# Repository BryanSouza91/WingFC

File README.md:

# WingFC

> [!WARNING]
> ### ⚠️ REPOSITORY ARCHIVED & SUPERSEDED
> This original TinyGo implementation of WingFC has been archived and is preserved for historical reference.
>
> Active development has transitioned into two dedicated, first-class repositories within the **Ferrox-RC** ecosystem:
> - 🦀 **Firmware:** [**ferrox-rc/wingfc-rs**](https://github.com/ferrox-rc/wingfc-rs) — High-performance, zero-latency bare-metal Rust flight controller firmware for sub-250g wings and UAVs.
> - ⚡ **Hardware:** [**ferrox-rc/wingfc-hardware**](https://github.com/ferrox-rc/wingfc-hardware) — KiCad schematics, 4-layer PCB layouts, 3D mechanical models, and carrier board designs.

### Historical Version 0.3.0 (TinyGo Prototype)

WingFC is a specialized open-source embedded flight controller designed specifically for the rapidly growing sub-250g flying wing FPV (First-Person-View) market. The project's core mission is to provide a reliable, user-friendly, and highly customizable solution for hobbyists and enthusiasts building ultra-lightweight Unmanned Aerial Vehicles (UAVs).

The emphasis on the sub-250g weight class is a direct response to a patchwork of international regulations. Many aviation authorities worldwide, including the Federal Aviation Administration (FAA) in the U.S. and the European Union Aviation Safety Agency (EASA), have established a 250-gram weight threshold as a key regulatory distinction. UAVs below this weight are often considered a lower risk and are exempt from stricter rules, such as mandatory registration, Remote ID requirements, or more complex pilot licensing. By focusing on this market segment, WingFC enables hobbyists to build and fly FPV aircraft that can be legally operated in more places and with fewer bureaucratic hurdles, significantly lowering the barrier to entry for beginners and experienced pilots alike.

Powered by TinyGo, a Go compiler for microcontrollers, WingFC offers a robust and stable software platform. The project provides essential flight control features for elevon-equipped fixed-wing aircraft, including:

- **Stabilization Modes**: Offers flight stabilization to assist pilots, particularly for smooth, cinematic FPV footage and relaxed cruising.

- **Mixing**: Handles the complex mixing of aileron and elevator inputs for a fixed-wing flying wing platform, simplifying the aircraft's setup.

- **Safety Features**: Incorporates failsafe mechanisms to protect the aircraft and others in the event of signal loss.

- **Receiver Protocol Support**: Ensures broad compatibility with popular FPV communication standards, including FlySky's iBus, TBS's CRSF, and the open-source ELRS protocol, which is highly valued for its long-range capabilities and low latency in the FPV community.

The flight controller is engineered for a seamless integration into FPV flying wing airframes like the ZOHD Dart 250G or Alight Wing Aeronautics Flik, a prominent model in this market. The hardware's choice of the Seeed Studio Xiao nRF52840 Sense with an onboard IMU aligns with the project's goal of creating a compact, lightweight, and high-performance control system for these specific FPV drones.

## Getting Started

These instructions will get you a copy of the project up and running on your local machine for development and testing purposes. See deployment for notes on how to deploy the project on a live system.

### Prerequisites

What things you need to install the software and how to install them

```
- Go (TinyGo)
- Supported microcontroller (see docs)
```

### Installing

[Download source code](https://github.com/BryanSouza91/WingFC/releases/tag/v0.3.0)
Extract source code then navigate to the top directory of the source.
```
cd firmware/src
```

Plug in WingFC board via USB-C 

When the filesystem shows up on your computer, flash firmware to your board

```
tinygo flash -target=xiao-ble -tags=<ibus,crsf> firmware/src
```

## Deployment

Add additional notes about how to deploy this on a live system

- Flash the firmware to your supported board
- Connect servos and sensors as described
- Power up and calibrate according to instructions

## Built With

### Software
• [TinyGo](https://tinygo.org/) - Go compiler for microcontrollers  
• [Go](https://golang.org/) - Language
### Hardware
• [Seeed Studio Xiao nrf52840 Sense](https://wiki.seeedstudio.com/XIAO_BLE/) - Xiao nrf52840 Sense microcontroller with onboard IMU

## Supported Receiver Protocols

WingFC supports multiple RC receiver protocols for maximum compatibility:

- **iBus** (FlySky): Supports up to 18 channels (FS-A8S, FS-iA6B)
- **CRSF** (TBS): Supports up to 16 channels
- **ELRS** (open-source): Supports up to 16 channels (uses CRSF build)

## Contributing

Please read [CONTRIBUTING.md](https://github.com/BryanSouza91/WingFC/CONTRIBUTING.md) for details on our code of conduct, and the process for submitting pull requests to us.

## Versioning

We use [SemVer](http://semver.org/) for versioning. For the versions available, see the [tags on this repository](https://github.com/BryanSouza91/WingFC/tags).

## Authors

• Bryan Souza - Initial work - [BryanSouza91](https://github.com/BryanSouza91)
• truglodite - CRSF/ELRS finalization, feature additions - [truglodite](https://github.com/truglodite)

See also the list of [contributors](https://github.com/BryanSouza91/WingFC/contributors) who participated in this project.

## License

This project is licensed under the MIT License - see the [LICENSE](https://github.com/BryanSouza91/WingFC/blob/main/LICENSE) file for details

## Acknowledgments

• Hat tip to anyone whose code was used  
• Inspiration from open-source flight controllers  
• TinyGo and Go communities

## Footer

[GitHub Homepage](https://github.com/)
# WingFC

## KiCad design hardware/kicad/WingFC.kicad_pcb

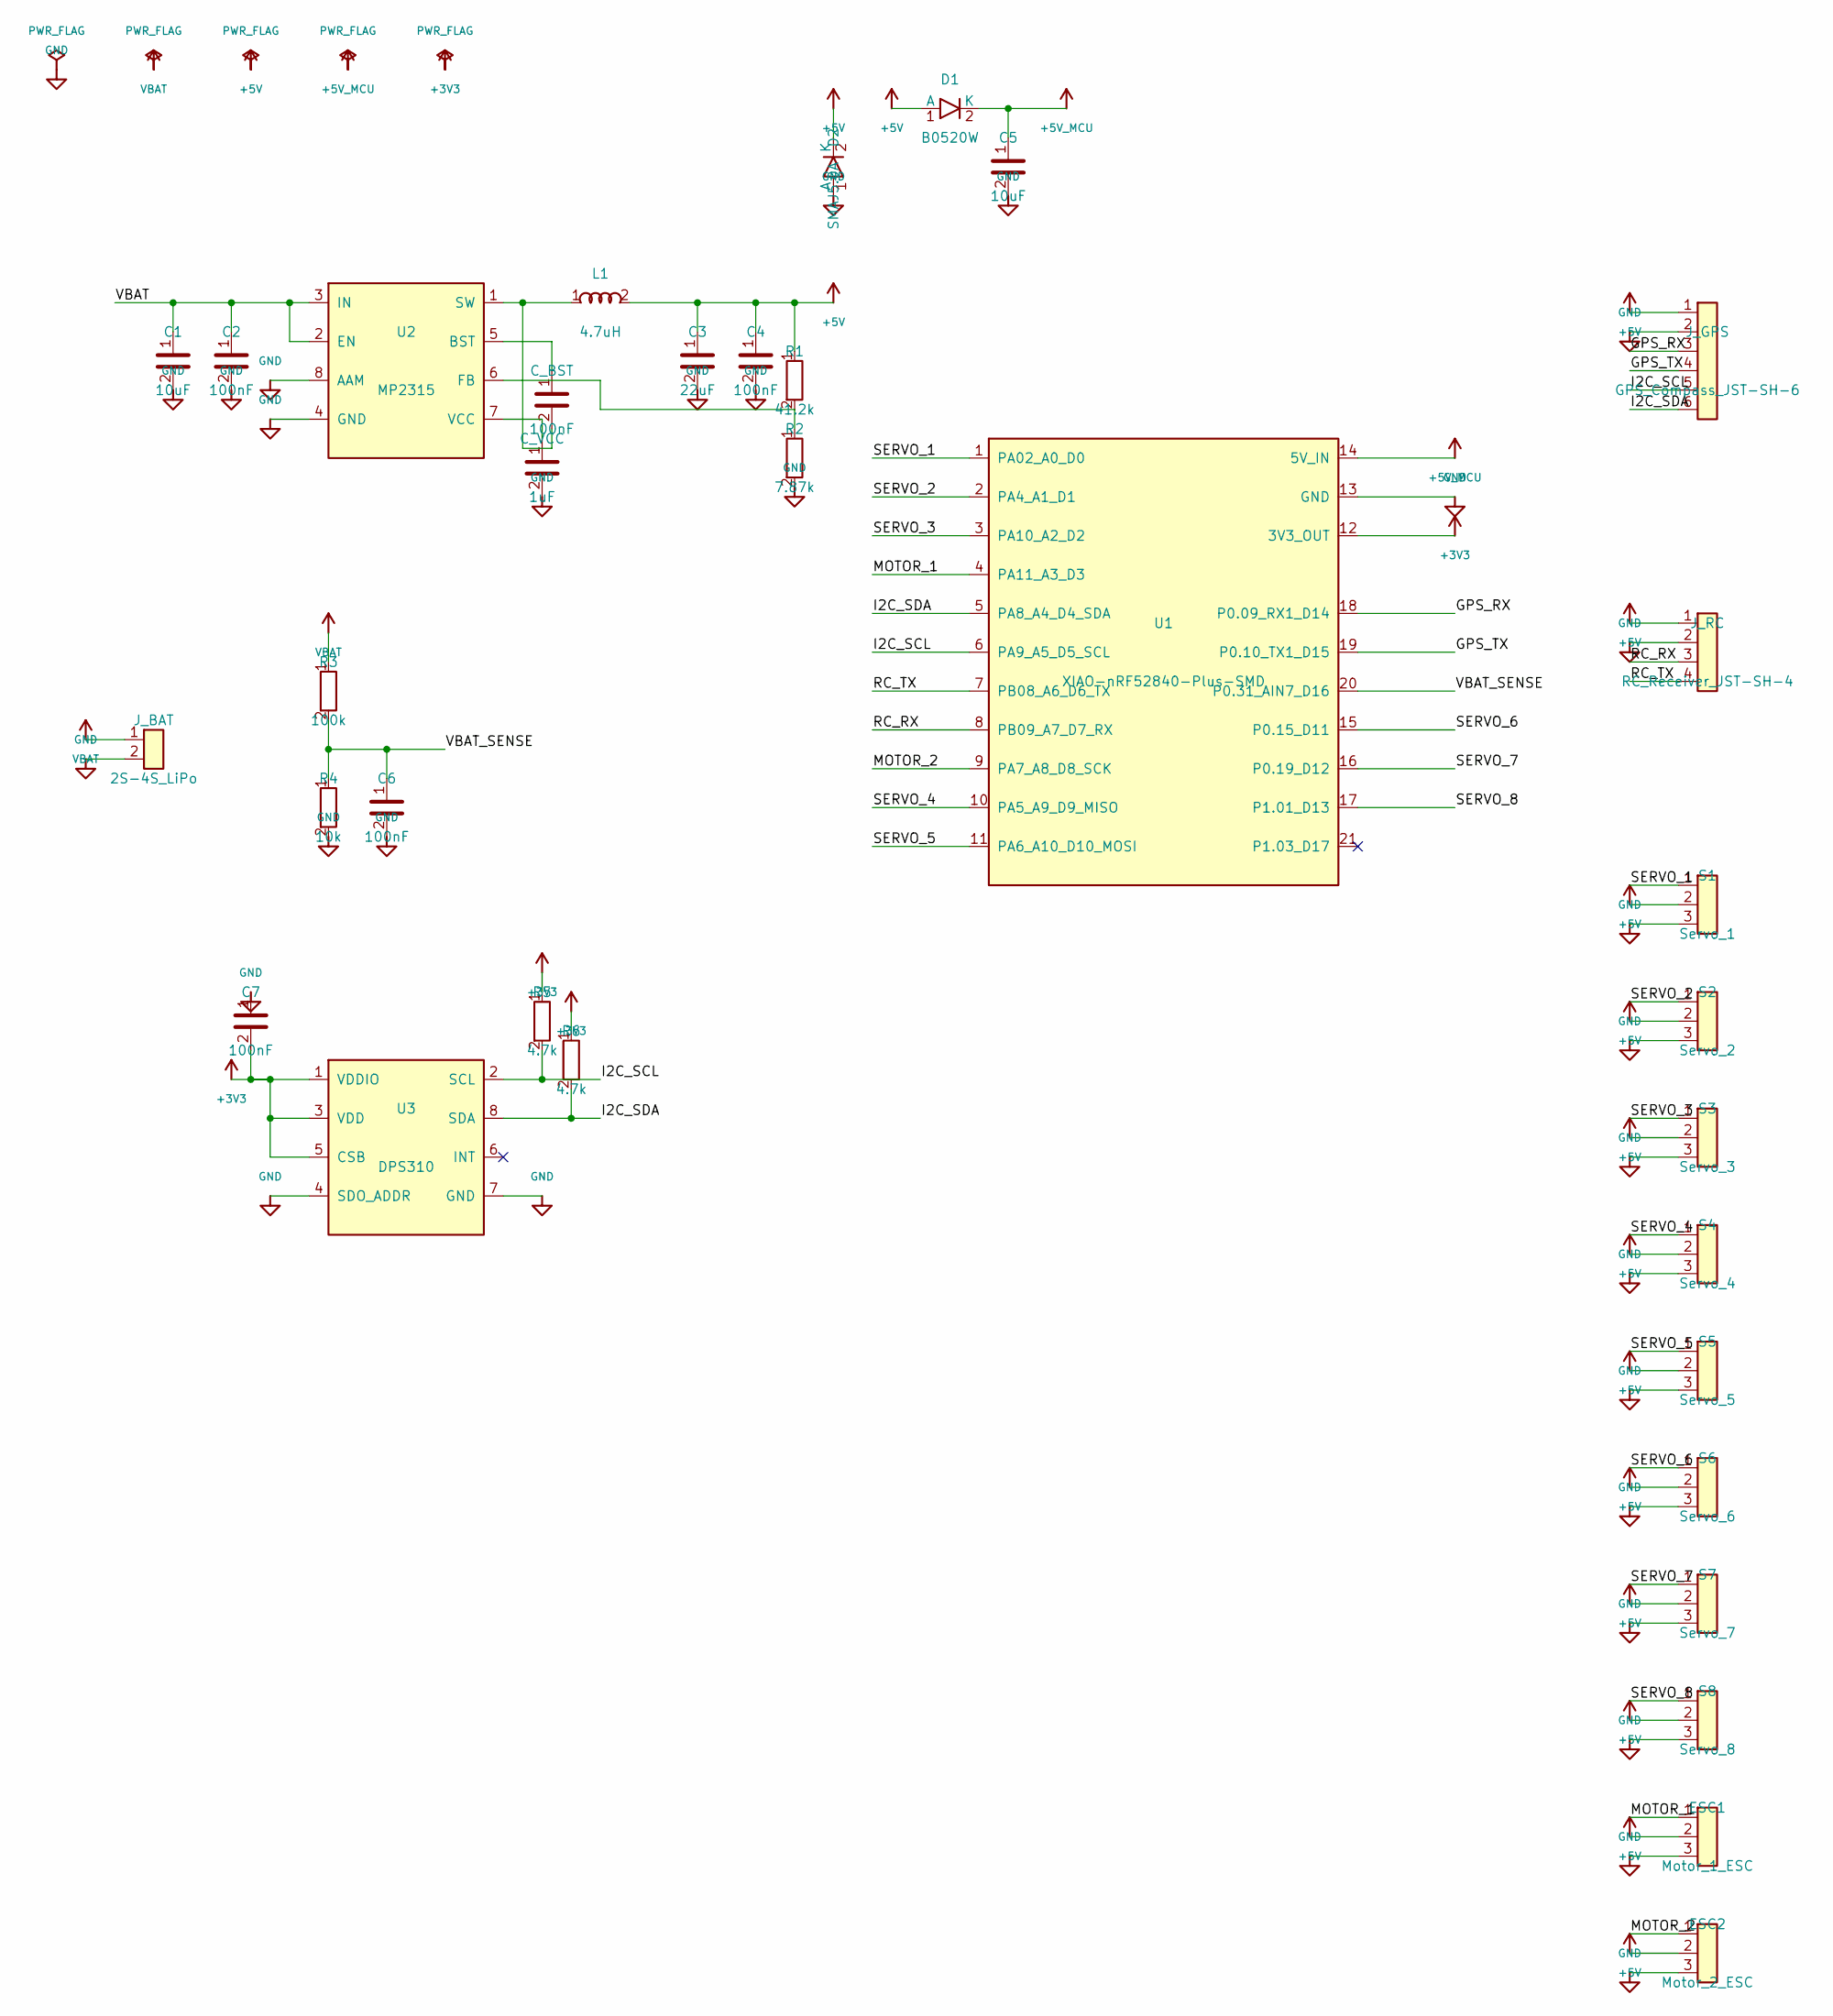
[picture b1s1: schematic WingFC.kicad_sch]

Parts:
C1, C5: 10uF; C_0805_2012Metric
C2, C4, C6, C7: 100nF; C_0603_1608Metric
C3: 22uF; C_0805_2012Metric
C_BST: 100nF; C_0603_1608Metric
C_VCC: 1uF; C_0603_1608Metric
D1: B0520W; D_SOD-123
D2: SMAJ5.0A; D_SMA
ESC1: Motor_1_ESC; PinHeader_1x03_P2.54mm_Vertical
ESC2: Motor_2_ESC; PinHeader_1x03_P2.54mm_Vertical
J_BAT: 2S-4S_LiPo; SolderWire-0.75sqmm_1x02_P4.8mm_D1.2mm_OD2.3mm
J_GPS: GPS_Compass_JST-SH-6; JST_SH_SM06B-SRSS-TB_1x06-1MP_P1.00mm_Horizontal
J_RC: RC_Receiver_JST-SH-4; JST_SH_SM04B-SRSS-TB_1x04-1MP_P1.00mm_Horizontal
L1: 4.7uH; L_Bourns_SRN4018
R1: 41.2k; R_0603_1608Metric
R2: 7.87k; R_0603_1608Metric
R3: 100k; R_0603_1608Metric
R4: 10k; R_0603_1608Metric
R5, R6: 4.7k; R_0603_1608Metric
S1: Servo_1; PinHeader_1x03_P2.54mm_Vertical
S2: Servo_2; PinHeader_1x03_P2.54mm_Vertical
S3: Servo_3; PinHeader_1x03_P2.54mm_Vertical
S4: Servo_4; PinHeader_1x03_P2.54mm_Vertical
S5: Servo_5; PinHeader_1x03_P2.54mm_Vertical
S6: Servo_6; PinHeader_1x03_P2.54mm_Vertical
S7: Servo_7; PinHeader_1x03_P2.54mm_Vertical
S8: Servo_8; PinHeader_1x03_P2.54mm_Vertical
U1: XIAO-nRF52840-Plus-SMD
U2: MP2315; TSOT-23-8
U3: DPS310; Infineon_PG-VLGA-8-1_2.0x2.5mm_P0.65mm

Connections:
+3V3: C7.2, R5.1, R6.1, U1.12 (3V3_OUT), U3.1 (VDDIO), U3.3 (VDD), U3.5 (CSB)
+5V: C3.1, C4.1, D1.1 (A), D2.2 (K), ESC1.2, ESC2.2, J_GPS.1, J_RC.1, L1.2, R1.1, S1.2, S2.2, S3.2, S4.2, S5.2, S6.2, S7.2, S8.2
+5V_MCU: C5.1, D1.2 (K), U1.14 (5V_IN)
/GPS_RX: J_GPS.3, U1.18 (P0.09_RX1_D14)
/GPS_TX: J_GPS.4, U1.19 (P0.10_TX1_D15)
/I2C_SCL: J_GPS.5, R5.2, U1.6 (PA9_A5_D5_SCL), U3.2 (SCL)
/I2C_SDA: J_GPS.6, R6.2, U1.5 (PA8_A4_D4_SDA), U3.8 (SDA)
/MOTOR_1: ESC1.1, U1.4 (PA11_A3_D3)
/MOTOR_2: ESC2.1, U1.9 (PA7_A8_D8_SCK)
/RC_RX: J_RC.3, U1.8 (PB09_A7_D7_RX)
/RC_TX: J_RC.4, U1.7 (PB08_A6_D6_TX)
/SERVO_1: S1.1, U1.1 (PA02_A0_D0)
/SERVO_2: S2.1, U1.2 (PA4_A1_D1)
/SERVO_3: S3.1, U1.3 (PA10_A2_D2)
/SERVO_4: S4.1, U1.10 (PA5_A9_D9_MISO)
/SERVO_5: S5.1, U1.11 (PA6_A10_D10_MOSI)
/SERVO_6: S6.1, U1.15 (P0.15_D11)
/SERVO_7: S7.1, U1.16 (P0.19_D12)
/SERVO_8: S8.1, U1.17 (P1.01_D13)
/VBAT_SENSE: C6.1, R3.2, R4.1, U1.20 (P0.31_AIN7_D16)
GND: C1.2, C2.2, C3.2, C4.2, C5.2, C6.2, C7.1, C_VCC.2, D2.1 (A), ESC1.3, ESC2.3, J_BAT.2, J_GPS.2, J_RC.2, R2.2, R4.2, S1.3, S2.3, S3.3, S4.3, S5.3, S6.3, S7.3, S8.3, U1.13 (GND), U2.4 (GND), U2.8 (AAM), U3.4 (SDO_ADDR), U3.7 (GND)
unnamed: C_BST.1, U2.5 (BST)
unnamed: R1.2, R2.1, U2.6 (FB)
unnamed: C_BST.2, L1.1, U2.1 (SW)
unnamed: C_VCC.1, U2.7 (VCC)
VBAT: C1.1, C2.1, J_BAT.1, R3.1, U2.2 (EN), U2.3 (IN)

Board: 4 copper layers, 38 parts (21 on the bottom side), 26 nets, no tracks yet.

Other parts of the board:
H1, H2, H3, H4: MountingHole_2.2mm_M2

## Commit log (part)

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2025-09-11 initial commit; POC codebase;
2025-09-11 added missing logic for throttle control; added adjustable constants for configuration;
2025-09-11 fixed error of units between degs and rads for roll and pitch rates; added .gitignore;
2025-09-11 reordered logic of WAITING state; added missing lastFlightState logic;
2025-09-11 added README;
2025-09-11 updated README;
2025-09-12 added information and versioning to startup;
2025-09-12 Updated to v0.0.2;
2025-09-12 restructured directory and file nomenclature;
2025-09-13 added LICENSE and updated README.md;
2025-09-13 added CONTRIBUTING.md;
2025-09-13 fixed logic of switch breakout between states based on conditions;
2025-09-13 updated comment in CALIBRATING state;
2025-09-14 WIP: Adding multiprotocol support;
2025-09-14 updated README for multiprotocol support; refactored main.go;
2025-09-14 updated README for multiprotocol support;
2025-09-14 fixed some minor issues; refactored channel mappings for easier config;
2025-09-14 refactored configuration to config.go;
2025-09-15 fixed duplicate declaration; moved 'Channels' to main.go eliminating channels.go;
2025-09-15 Fixed major logical issue with the flight mode elevon mixing; refactored config.go;
2025-09-15 refactored order of flight mode logic;
2025-09-15 fixed uncalibrated mode functionality;
2025-09-15 version upgrade to 0.1.0;
2025-09-15 v0.1.0;
2025-09-15 worked on PCB design;
2025-09-15 removed kicad backups;
2025-09-16 converted to 4-layer PCB;
2025-09-16 fixed small error on PCB;
2025-09-17 debugging the iBus sync issues;
2025-09-18 Major Refactor; aiming to solve latency issues;
2025-09-18 tested and functioning minimal iBus version; removed multiprotocol support and refactored;
2025-09-18 tested further and double checked unit continuity;
2025-09-18 Refactored main.go for legibility and completness;
2025-09-18 version upgrade to v0.1.1; non-backwards compatible single protocol complete refactor and restructure; functioning well;
2025-09-19 Added EMA Low-Pass Filter on IMU in hopes to help with drift and inaccuracies;
2025-09-19 Added support for CRSF protocol with buildtime tag;
2025-09-19 refactored to prepare for merge;
2025-09-19 added BUILD.md; updated README.md
2025-09-19 Release Version 0.1.2; Multi-Protocol Support
2025-09-19 Fixed duplicate function declarations in helpers.go;
2025-09-19 bring up to date with ; hardware updates need to be merged;
2025-09-20 fixed some major bugs related to packet size with CRSF protocol;
2025-09-20 added mapRangeFloat and mapRangeInt;
2025-09-20 light refactoring; added failsafe logic; added manual mode logic; added arming/disarming logic;
2025-09-20 refactored generic mapRange func;
2025-09-21 Update BUILD.md
    removed escape characters
2025-09-21 converted flight control logic into state machine like previous versions;
2025-09-21 removed duplicate logic;
2025-09-21 fixed bug with receiver packet processing for iBus; fixed PWM high freq signal issue;
2025-09-22 Update README.md
    Extended summary for broader reach and better motivation
2025-09-22 fixed calibration issue;
2025-09-22 Update README.md
    Updated version
2025-09-23 updated baud rate for CRSF protocol;
2025-09-24 added firmware/tests for testing; Preliminary fix for CRSF;
2025-09-24 reformatted printed message for crsf test;
2025-09-24 updated checksum comment information;
2025-09-24 added delay to CRSF readReceiver loop to prevent blocking;
2025-09-24 added missing import;
2025-09-24 fixed comment;
2025-09-25 Built tests for CRSF protocol; tests pass but need to test on hardware;
2025-09-25 fixed loop bug(I moved function calls out of scope) causing crash;
2025-09-25 added delay for buffering data from uart for debugging;
2025-09-25 fixed CRSF Channels bug;
2025-09-26 Refactored main state machine;
2025-09-26 adjusted CALIBRATION state;
2025-09-26 more debugging printing;
2025-09-30 added comments and adjusted tests output;
2025-10-04 updated PCB layout; planning to add GPS thru UART1 and I2C0;
2025-10-04 updated schematic to include GPS connector;
2025-10-04 updated GPS connector in schematic;
2025-10-05 updated schematic for Sense Plus and GPS support; added GPS connector to PCB;
2026-02-22 Changed the packet channel to be buffered;
2026-02-23 Fixed issue with LPF implementation thanks to @AKlenk13
2026-03-01 Updated tests to match src;
2026-03-01 Ready for version 0.2.3 release;
2026-03-03 added error handling logic;
2026-03-04 Added Reset method for PIDController;
2026-03-10 Add manual mode config and processing with pid reset.
2026-03-10 Fix pid reset to actually reset the pid controllers
2026-03-10 Added 8 color LED helper. Added boot check/err LED indicators to main.
2026-03-11 Add resetPID component in main; oops.
2026-03-12 Convert channels from ticks to microseconds in crsf.go
2026-03-12 added logic to crsf.go to output channelValues in microseconds;
2026-03-12 fixed the mathematic logic in crsf.go to output channelValues in microseconds;
2026-03-12 fixed the mathematic logic in src/crsf.go to output channelValues in microseconds;
2026-03-12 updated comments for accuracy;
2026-03-14 fixed usToTicks in crsf.go;
2026-03-30 Copy LED changes from dev-subtrim-led to dev-init.
2026-04-02 MAJOR REFACTOR; Entire codebase refactored to use dependency injection; Hardware abstraction layer added; Initialization refactored;
2026-04-02 Release Version 0.3.0
2026-04-03 updated LED system to use the same dependency injection methods; added DigitalPin interface;
2026-04-03 fixed error in NewLEDController in main.go;
2026-04-03 updated matrix and kalman for 3x3 matrix compatibility; updated main loop to 200Hz as a major performance boost;
2026-04-03 fixed disarm mode, now only ESC is disarmed; added documentation to pid.go for unit continuity refer to UNIT_ANALYSIS.md;
2026-04-04 Autopilot Claude Haiku 4.5 testing refactor start;
2026-04-04 updated readReciever to true dependecy injection;
2026-04-04 removed duplicate PWM adapter;
2026-04-04 Added subtrims and endpoints;
2026-04-04 adding Flowchart and a few other documents;
2026-04-04 adding Flowchart mermaid.js file;
2026-04-04 adding math optimization report;
2026-04-04 edited math optimization report; updated other docs;
2026-04-05 ran gofmt;
2026-04-05 eliminated the stdlib math in favor of tinymath that uses float32 for the nrf52840 FPU;
2026-04-05 updated config.go for float32 compatibility;
2026-04-05 converted Low-Pass Filter to single cycle bitshift operation from math operation;
2026-04-05 added variable declarations for Low-Pass Filter;
2026-04-05 formatted helpers.go;
2026-04-05 added subtrims and endpoints; added tuning to the flight contol loop;
2026-04-05 added more tuning parameters; added board orientation support;
2026-04-05 corrected calibration with correct applications of the filters and orientation;
2026-04-05 report for Airframe Type implementation;
2026-04-09 added ApplyMixer for other airframe type; updates to kalman and matrix;
2026-04-10 updated comments on config.go;
2026-04-11 moved call to initPWMs to be earliest; addressed the ESC initialization error with initPWM Set call;
2026-04-11 fixed build error;
2026-04-11 added ESC_CALIBRATION state;
2026-04-11 fixed error with flightstate;
2026-04-11 added No Motion No Integration (NMNI) algorithm for Yaw; Double checked units and corrected as necessary;
2026-04-11 added absolute value calc to NMNI filter;
2026-04-11 added some IMU related documents;
2026-04-11 added DSHOT support;
2026-04-11 fixed DSHOT implementation;
2026-04-12 added dshot tests but they do not pass... they need work;
2026-06-11 moved airframe declarations to mixer.go and updated comments for config.go;
2026-06-13 started GPS implementation;
2026-06-21 built out Return-To-Home and GPS logic; Main state machine logic needs to be reevaluated;
